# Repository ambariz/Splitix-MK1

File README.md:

# Splitix MK1

A custom, split mechanical keyboard with modular design, it can be used as a split keyboard or joined together and used like a regular keyboard.

Inspired by the split, futuristic keyboard used by Tony Stark in Iron Man, this project explores that concept in a practical, physical form. Splitix MK1 is the first iteration, focused on building a solid foundation before moving towards more advanced designs.

It features a custom PCB designed in KiCad, per-key NeoPixel RGB lighting, an integrated display, and a rotary encoder. The board also includes battery support with voltage monitoring.

The design includes a fully hand-routed PCB with custom footprints and a skeletal 3D-printed case that enhances the lighting and overall aesthetic.

This project is part of a larger journey toward creating a more advanced, Iron Man - inspired keyboard in future iterations.

| Left Build (without case) | Right Build (without case) |
|-----------|------------|
|  |  |

# Features

- Split / Modular (can be joined and used as a single keyboard)
- Wireless (Bluetooth via NRF52840)
- ZMK Firmware
- Hotswappable
- Per-key NeoPixel RGB
- Rotary Encoder
- Integrated Display
- Skeletal 3D-printed case (M3 mount)

## CAD

> **Note:**
> This is a skeletal open case design that includes only the base structure. It is designed to hold the PCB securely while keeping the overall form minimal and exposing the components, especially the RGB lighting. The open design enhances visibility of the internals and lighting, while support pillars and M3 mounts provide the necessary structural stability.

| Left | Right |
|------|-------|
|  |  |
|  |  |
|  |  |

## PCB

> **Note:**  
> The PCB is designed as a single board with mouse bite connections, allowing it to be snapped into left and right halves after fabrication.

## Schematic

> **Note:**  
> The preview images may be scaled down and lose detail. Use the PDF below for a clear, full-resolution view.

<p align="center">
  
</p>

| Left | Right |
|------|-------|
|  |  |

## ZMK Keymap

## BOM

| Product | Quantity | Source | Price (INR) | Link |
| :--- | :--- | :--- | :--- | :--- |
| ProMicro NRF52840 | 2 | Robu | 1516 | [Product Link](https://robu.in/product/promicro-nrf52840-development-board/) <br> OR <br> [Product Link](https://robu.in/product/pro-micro-nrf52840-development-board-compatible-with-nicenano-v2-0/) <br> OR <br> [Product Link](https://probots.co.in/pro-micro-nrf52840-development-board-compatible-with-nice-nano-v2-0.html)|
| Hongyan EC11H 7CE20P1ZD20 | 2 | Robu | 110 | [Product Link](https://robu.in/product/hongyan-ec11h-7ce20p1zd20-rotary-encoder-with-push-button-switch-vertical-plug-in-5-pin/) |
| EC11 Rotary Encoder Knob (D-shaft) | 2 | Robu | 58 | [Product Link](https://robu.in/product/potentiometer-knob-rotary-switch-cap-black-color-pack-of-5-pcs/) |
| 0.96" / 1.3" I2C OLED | 2 | Robu | 312 | [Product Link](https://robu.in/product/0-96-inch-yellow-yellow-blue-oled-lcd-led-display-module/) <br> OR <br> [Product Link](https://robu.in/product/1-3-inch-i2c-iic-4-pin-oled-display-module-with-vcc-gnd-blue/) |
| WS2812B 16-LED Ring (Neopixel) | 6 (rings) / 90 (individual) | Robu / Ktron | 546 | [Product Link](https://robu.in/product/16bit-ws2812b-5050-rgb-led-built-in-full-color-driving-lights-circular-development-board/) <br> OR <br> [Product Link](https://www.ktron.in/product/ws2812b-rgb-smd-5050-led/?v=c86ee0d9d7ed) |
| 330Ω Resistor | 4 | Robu | 1.16 | [Product Link](https://robu.in/product/330-ohm-0-25w-metal-film-resistor-pack-of-100/) |
| 806kΩ Resistor | 2 | Robu | 1.24 | [Product Link](https://robu.in/product/mcmf0w4ff8203a50-multicomp-pro-metal-film-resistor-820kohm-250mw-1/) |
| 2MΩ Resistor | 2 | Amazon | 198 | [Product Link](https://www.amazon.in/Electronic-Spices-Tolerance-Through-Resistors/dp/B0BDDRD9DN) |
| 100µF 0805 Capacitor | 6 | Robu | 270 | [Product Link](https://robu.in/product/cl21a107mqynnwe-samsang-6-3v-100uf-x5r-%C2%B120-0805-multilayer-ceramic-capacitors-mlcc-smd-smt-rohs/) |
| 0.1µF (100nF) 0805 Capacitor | 95 | Robu | 145.35 | [Product Link](https://robu.in/product/cc0805jrx7r9bb104-yageo-smd-multilayer-ceramic-capacitor-0-1-%C2%B5f-50-v-0805-2012-metric-%C2%B1-5-x7r-cc-series/) |
| Mechanical Key Switches (MX Compatible) | 75 | StacksKB | 2398 | [Product Link](https://stackskb.com/store/akko-creamy-cyan-switch-pack-of-45-pre-order/) |
| Keycaps (MX Compatible) | 1 set | StacksKB | 1299 | [Product Link](https://stackskb.com/store/veekos-gradient-keycaps-cherry-profile-135-keys/) |
| Hotswap Sockets (Kailh MX) | 75 | StacksKB | 750 | [Product Link](https://stackskb.com/store/ttc-pokayoke-hotswap-sockets-v2-10000-cycles/) |
| 1N4148 Diodes | 80 | StacksKB | 120 | [Product Link](https://stackskb.com/store/1n4148-through-hole-diode/) |
| Li-ion Battery 1500mAh | 2 | Robu | 502 | [Product Link](https://robu.in/product/nova-803450-1500mah-3-7v-lipo-battery-pack/) |
| JST-PH 2-pin Connector | 2 | Robu | 2.84 | [Product Link](https://robu.in/product/jst-sh-2-pin-connector-2mm-pitch/) |
| TP4056 Type-C Charging Module | 2 | Robu | 28 | [Product Link](https://robu.in/product/tp4056-1a-li-ion-lithium-battery-charging-module-with-current-protection-type-c/) |
| Slide Switch SS-12D03 | 2 | Robu | 6 | [Product Link](https://robu.in/product/slide-switch-ss-12d03-1p2t/) |
| Keyboard PCB Left | 5 | Robu | 2500 | [Product Link](https://robu.in/product/online-pcb-manufacturing-service/) |
| Keyboard PCB Right | 5 | Robu | 2500 | [Product Link](https://robu.in/product/online-pcb-manufacturing-service/) |
| Keyboard Case (3D Print) | 1 | Robu | 530 | [Product Link](https://robu.in/product/3d-printing-service/) |
| Screws | 15 | Generic |  | Any M3 screws will work |

---

### Total Cost (Maximum)

**₹13,793.59**

> Includes all components for full build.

---

# Mechanical Keyboard Keycap Profiles

---

### Quick Comparison
| Profile | Key Features | Best Used For |
| :--- | :--- | :--- |
| **Cherry** | Ergonomic height, reduces accidental touches. | All-around daily use. |
| **OEM** | Standard height, crisp typing sound. | Linear switches and gaming. |
| **XDA** | Uniform height, large surface area. | Tactile switches, long typing sessions. |
| **DSA** | Very low, uniform height. | Minimalist builds and customization. |
| **MDA** | Stepped uniform profile, textured feel. | Ergonomic long-form typing. |
| **SA** | Tallest profile, spherical sculpt. | Aesthetics and deep sound (requires wrist rest). |

---

> ### Note:
- **Tall Profiles (SA):** Better acoustics and aesthetics, but poor ergonomics without a wrist rest.  
- **Flat Profiles (XDA, DSA):** Easier to customize looks, but higher chance of mistyping.  
- **Sculpted Profiles (Cherry, OEM, MDA):** Best for typing speed and overall accuracy.  

---

# Keyswitch Selection Guide

| Type | Characteristics | Best For |
| :--- | :--- | :--- |
| **1️⃣ Linear** | Very smooth, no bump. Quiet unless bottom-out → nice thock | Gaming + smooth typing |
| **2️⃣ Tactile** | Noticeable bump mid-press. Balanced sound + feel | Typing |
| **3️⃣ Clicky** | Loud click + tactile bump. Very audible → polarizing | Enthusiasts who love feedback |
| **4️⃣ Low Profile** | Short travel → less thock. More functional than aesthetic | Portable/compact builds |
| **5️⃣ Silent Switches** | Dampened + muted. Almost no sound → office safe | Office environments |  

marbastlib
keyswitch kicad library
keyboard footprints placer
fabrucatuib toolkit

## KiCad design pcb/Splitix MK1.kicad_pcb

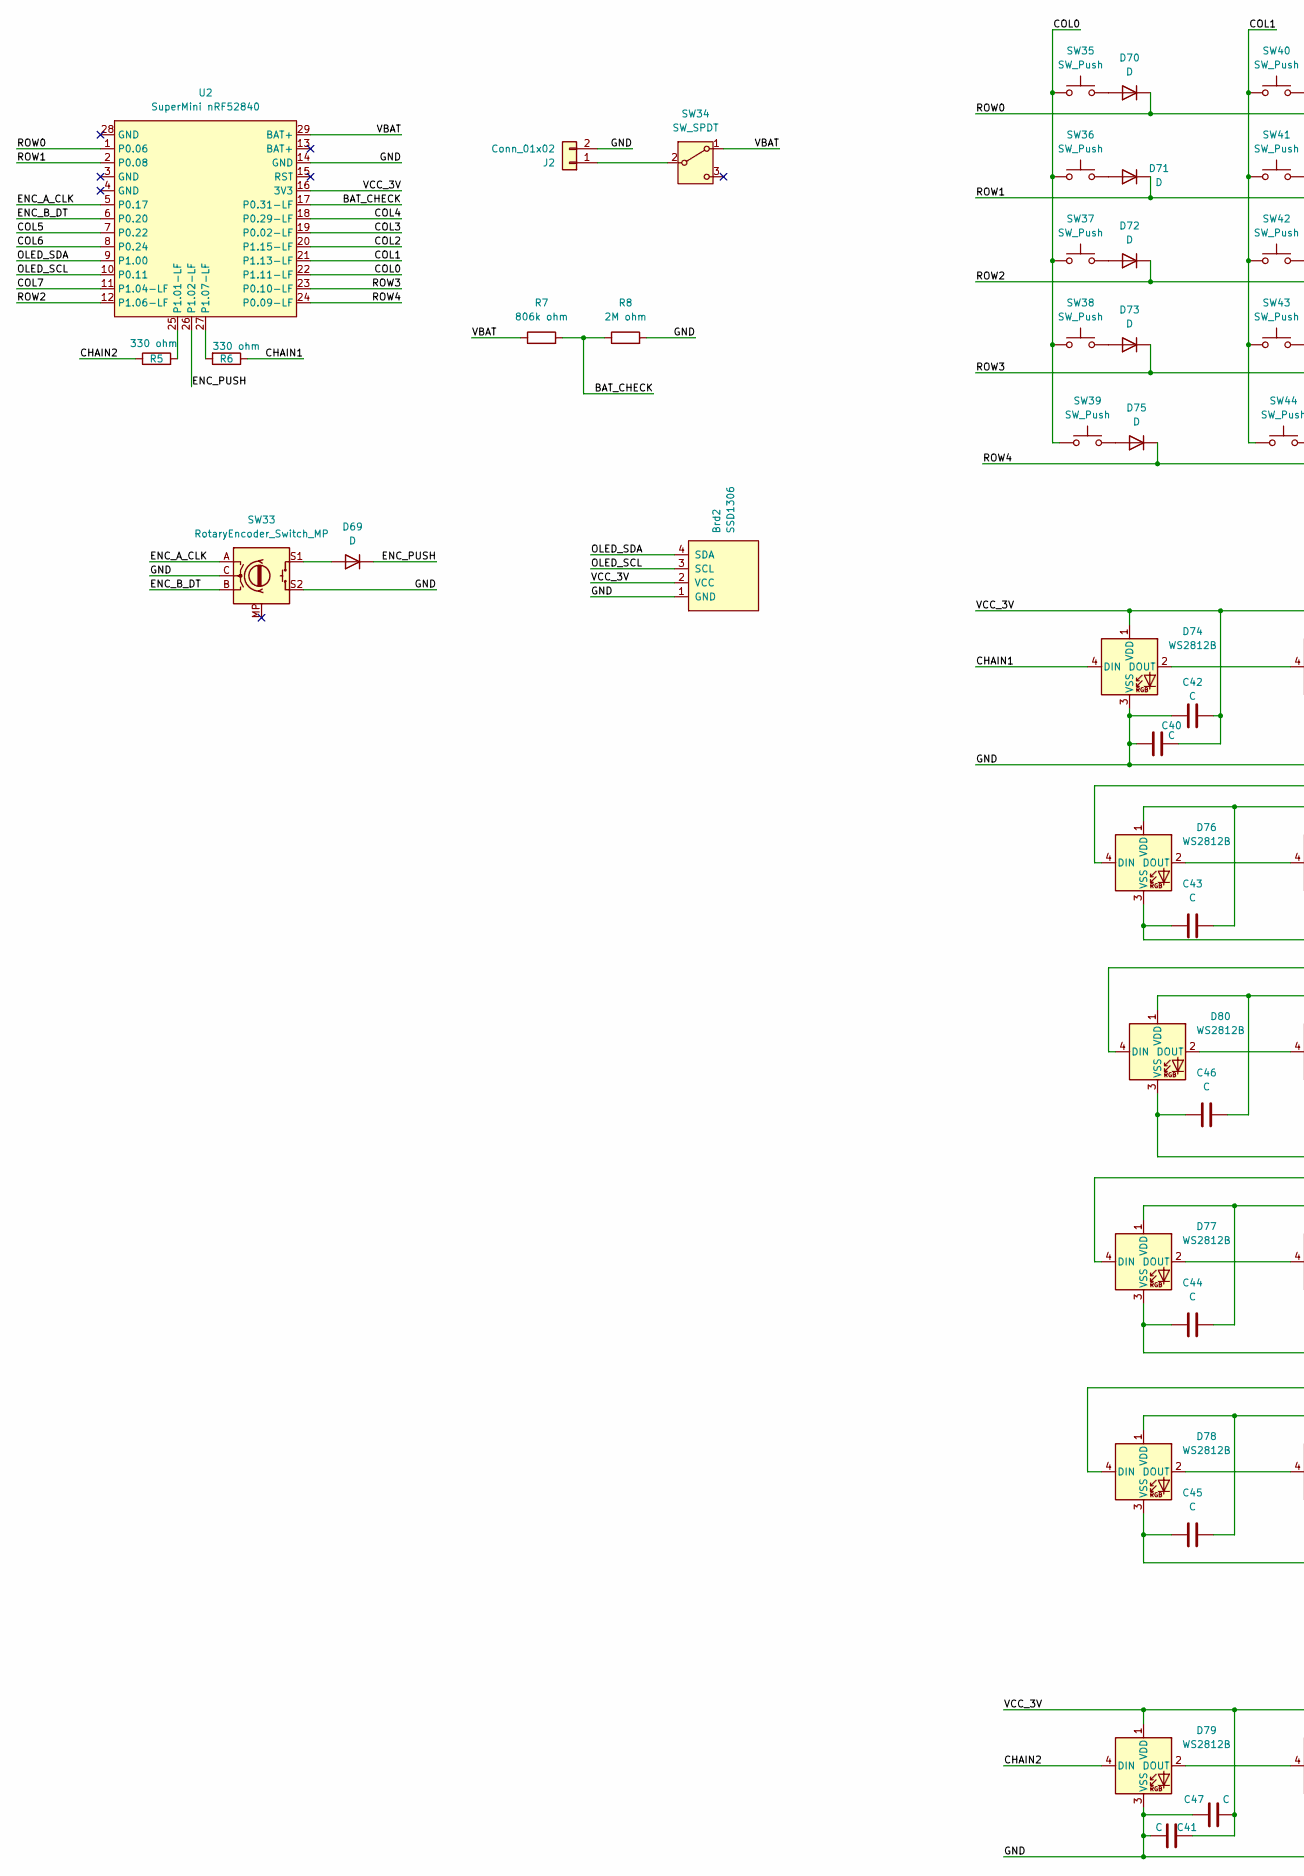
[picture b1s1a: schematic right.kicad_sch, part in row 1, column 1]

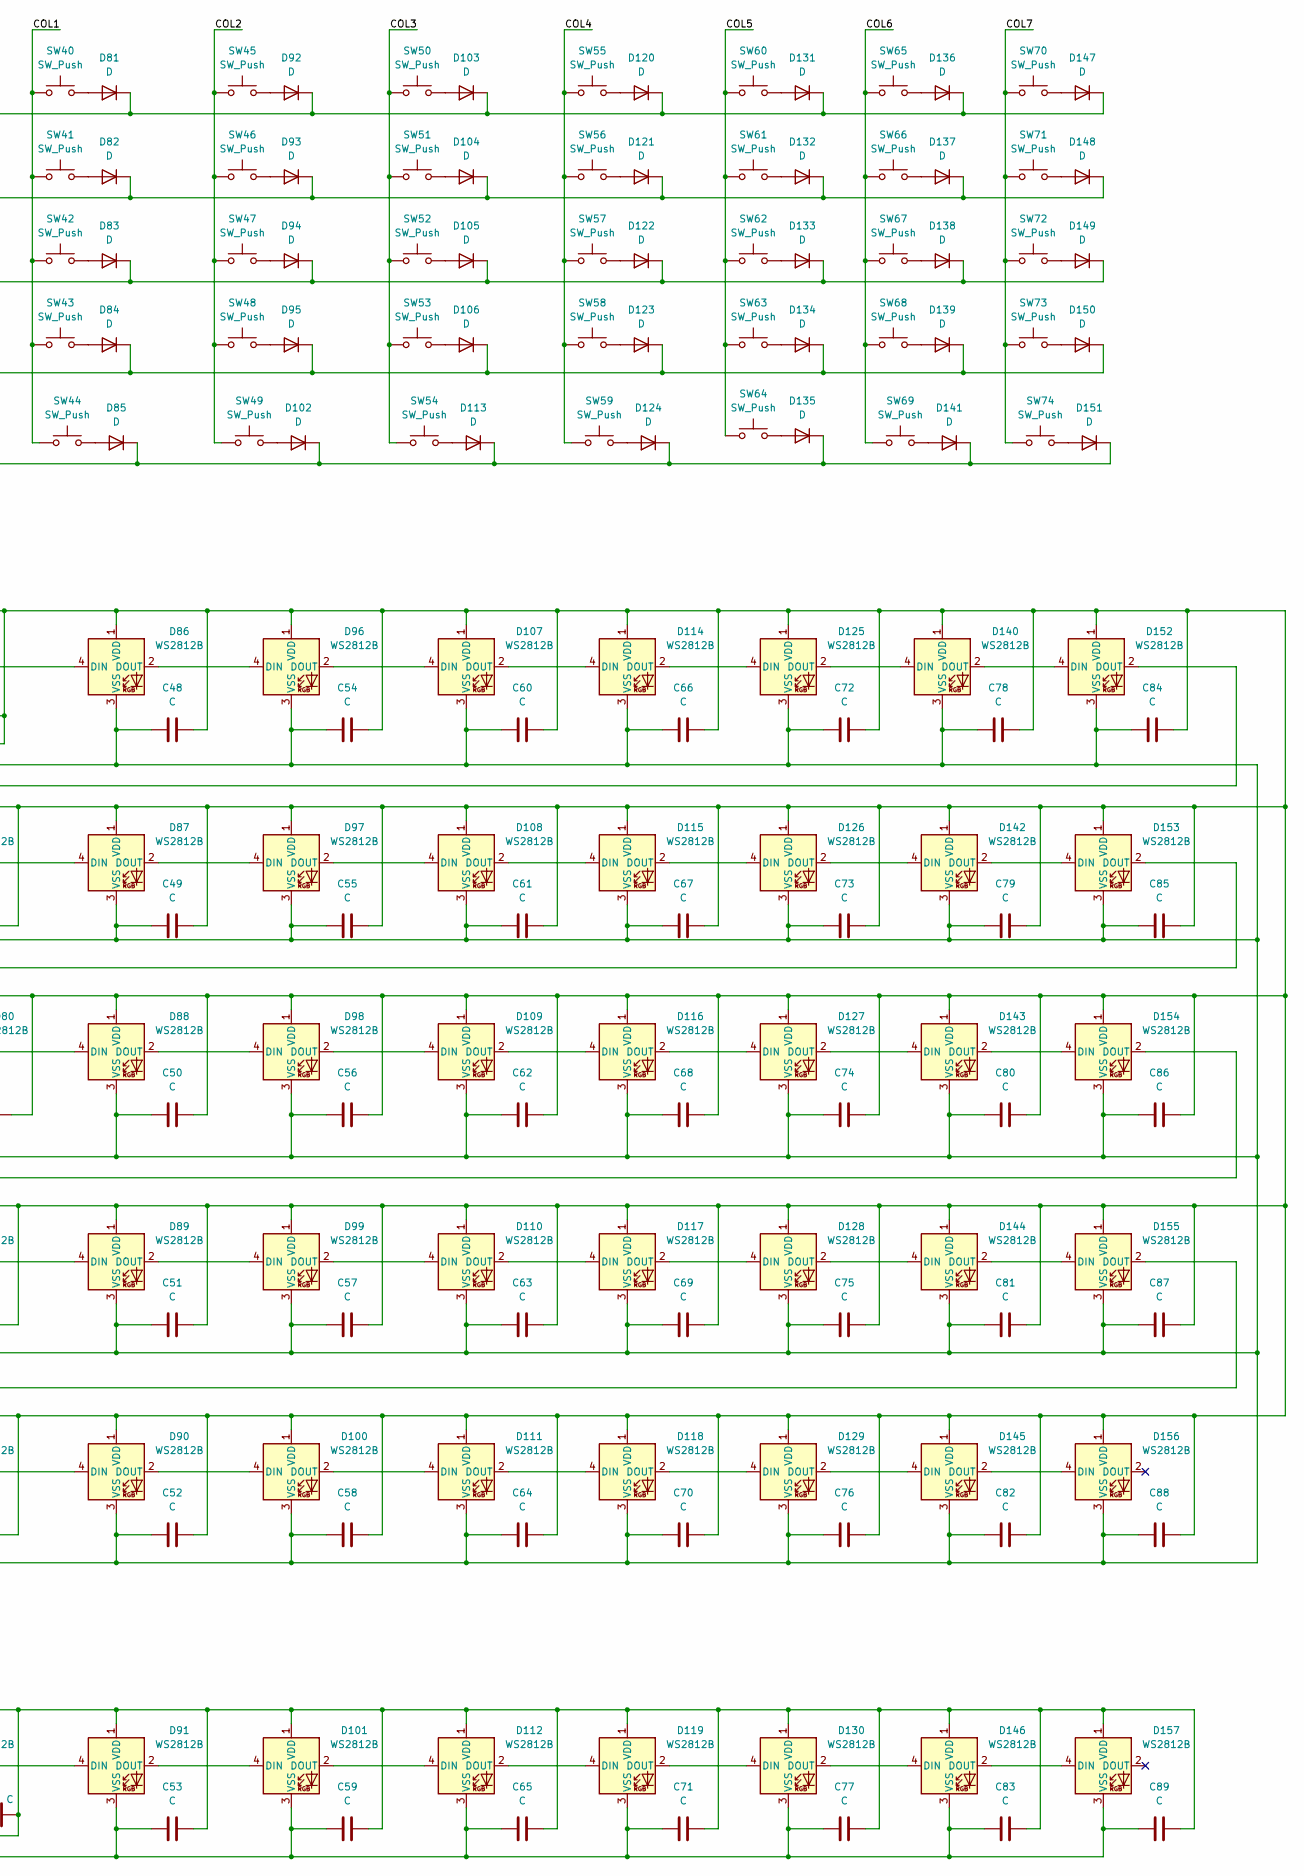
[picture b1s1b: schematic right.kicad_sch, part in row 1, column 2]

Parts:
Brd2: SSD1306; 128x64OLED
C40, C41, C42, C43, C44, C45, C46, C47, C48, C49, C50, C51, C52, C53, C54, C55, C56, C57, C58, C59, C60, C61, C62, C63, C64, C65, C66, C67, C68, C69, C70, C71, C72, C73, C74, C75, C76, C77, C78, C79, C80, C81, C82, C83, C84, C85, C86, C87, C88, C89: C; C_0805_2012Metric_Pad1.18x1.45mm_HandSolder
D69, D70, D71, D72, D73, D75, D81, D82, D83, D84, D85, D92, D93, D94, D95, D102, D103, D104, D105, D106, D113, D120, D121, D122, D123, D124, D131, D132, D133, D134, D135, D136, D137, D138, D139, D141, D147, D148, D149, D150, D151: D; D_DO-35_SOD27_P7.62mm_Horizontal
D74, D76, D77, D78, D80, D86, D87, D88, D89, D90, D96, D97, D98, D99, D100, D107, D108, D109, D110, D111, D114, D115, D116, D117, D118, D125, D126, D127, D128, D129, D140, D142, D143, D144, D145, D152, D153, D154, D155, D156: WS2812B; WS2812B_5050_reversed_SMD_edge
D79, D91, D101, D112, D119, D130, D146, D157: WS2812B; WS2812B_5050_reversed_SMD_strip
J2: Conn_01x02; PinHeader_1x02_P2.54mm_Vertical
R5, R6: 330 ohm; R_Axial_DIN0207_L6.3mm_D2.5mm_P7.62mm_Horizontal
R7: 806k ohm; R_Axial_DIN0207_L6.3mm_D2.5mm_P7.62mm_Horizontal
R8: 2M ohm; R_Axial_DIN0207_L6.3mm_D2.5mm_P7.62mm_Horizontal
SW33: RotaryEncoder_Switch_MP; RotaryEncoder_Alps_EC11E-Switch_Vertical_H20mm_CircularMoun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
SW34: SW_SPDT; PinHeader_1x03_P2.54mm_Vertical
SW35, SW36, SW37, SW38, SW40, SW41, SW42, SW43, SW45, SW46, SW47, SW48, SW49, SW50, SW51, SW52, SW53, SW54, SW55, SW56, SW57, SW58, SW59, SW60, SW61, SW62, SW64, SW66, SW68, SW69, SW70, SW72, SW73, SW74: SW_Push; SW_MX_HS_KS-2P02B01-01_1u
SW39: SW_Push; SW_MX_HS_KS-2P02B01-01_2.75u
SW44: SW_Push; SW_MX_HS_KS-2P02B01-01_1.25u
SW63: SW_Push; SW_MX_HS_KS-2P02B01-01_1.75u
SW65: SW_Push; SW_MX_HS_KS-2P02B01-01_2u
SW67: SW_Push; SW_MX_HS_KS-2P02B01-01_2.25u
SW71: SW_Push; SW_MX_HS_KS-2P02B01-01_1.5u
U2: SuperMini nRF52840; SuperMini_nRF52840_AH_USBup

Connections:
/right/BAT_CHECK: R7.2, R8.1, U2.17 (P0.31-LF)
/right/CHAIN1: D74.4 (DIN), R6.1
/right/CHAIN2: D79.4 (DIN), R5.1
/right/COL0: SW35.1, SW36.1, SW37.1, SW38.1, SW39.1, U2.22 (P1.11-LF)
/right/COL1: SW40.1, SW41.1, SW42.1, SW43.1, SW44.1, U2.21 (P1.13-LF)
/right/COL2: SW45.1, SW46.1, SW47.1, SW48.1, SW49.1, U2.20 (P1.15-LF)
/right/COL3: SW50.1, SW51.1, SW52.1, SW53.1, SW54.1, U2.19 (P0.02-LF)
/right/COL4: SW55.1, SW56.1, SW57.1, SW58.1, SW59.1, U2.18 (P0.29-LF)
/right/COL5: SW60.1, SW61.1, SW62.1, SW63.1, SW64.1, U2.7 (P0.22)
/right/COL6: SW65.1, SW66.1, SW67.1, SW68.1, SW69.1, U2.8 (P0.24)
/right/COL7: SW70.1, SW71.1, SW72.1, SW73.1, SW74.1, U2.11 (P1.04-LF)
/right/ENC_A_CLK: SW33.A, U2.5 (P0.17)
/right/ENC_B_DT: SW33.B, U2.6 (P0.20)
/right/ENC_PUSH: D69.1 (K), U2.26 (P1.02-LF)
/right/GND: Brd2.1 (GND), C40.1, C41.1, C42.1, C43.1, C44.1, C45.1, C46.1, C47.1, C48.1, C49.1, C50.1, C51.1, C52.1, C53.1, C54.1, C55.1, C56.1, C57.1, C58.1, C59.1, C60.1, C61.1, C62.1, C63.1, C64.1, C65.1, C66.1, C67.1, C68.1, C69.1, C70.1, C71.1, C72.1, C73.1, C74.1, C75.1, C76.1, C77.1, C78.1, C79.1, C80.1, C81.1, C82.1, C83.1, C84.1, C85.1, C86.1, C87.1, C88.1, C89.1, D74.3 (VSS), D76.3 (VSS), D77.3 (VSS), D78.3 (VSS), D79.3 (VSS), D80.3 (VSS), D86.3 (VSS), D87.3 (VSS), D88.3 (VSS), D89.3 (VSS), D90.3 (VSS), D91.3 (VSS), D96.3 (VSS), D97.3 (VSS), D98.3 (VSS), D99.3 (VSS), D100.3 (VSS), D101.3 (VSS), D107.3 (VSS), D108.3 (VSS), D109.3 (VSS), D110.3 (VSS), D111.3 (VSS), D112.3 (VSS), D114.3 (VSS), D115.3 (VSS), D116.3 (VSS), D117.3 (VSS), D118.3 (VSS), D119.3 (VSS), D125.3 (VSS), D126.3 (VSS), D127.3 (VSS), D128.3 (VSS), D129.3 (VSS), D130.3 (VSS), D140.3 (VSS), D142.3 (VSS), D143.3 (VSS), D144.3 (VSS), D145.3 (VSS), D146.3 (VSS), D152.3 (VSS), D153.3 (VSS), D154.3 (VSS), D155.3 (VSS), D156.3 (VSS), D157.3 (VSS), J2.2, R8.2, SW33.C, SW33.S2, U2.14 (GND)
/right/OLED_SCL: Brd2.3 (SCL), U2.10 (P0.11)
/right/OLED_SDA: Brd2.4 (SDA), U2.9 (P1.00)
/right/ROW0: D70.1 (K), D81.1 (K), D92.1 (K), D103.1 (K), D120.1 (K), D131.1 (K), D136.1 (K), D147.1 (K), U2.1 (P0.06)
/right/ROW1: D71.1 (K), D82.1 (K), D93.1 (K), D104.1 (K), D121.1 (K), D132.1 (K), D137.1 (K), D148.1 (K), U2.2 (P0.08)
/right/ROW2: D72.1 (K), D83.1 (K), D94.1 (K), D105.1 (K), D122.1 (K), D133.1 (K), D138.1 (K), D149.1 (K), U2.12 (P1.06-LF)
/right/ROW3: D73.1 (K), D84.1 (K), D95.1 (K), D106.1 (K), D123.1 (K), D134.1 (K), D139.1 (K), D150.1 (K), U2.23 (P0.10-LF)
/right/ROW4: D75.1 (K), D85.1 (K), D102.1 (K), D113.1 (K), D124.1 (K), D135.1 (K), D141.1 (K), D151.1 (K), U2.24 (P0.09-LF)
/right/VBAT: R7.1, SW34.1 (A), U2.29 (BAT+)
/right/VCC_3V: Brd2.2 (VCC), C40.2, C41.2, C42.2, C43.2, C44.2, C45.2, C46.2, C47.2, C48.2, C49.2, C50.2, C51.2, C52.2, C53.2, C54.2, C55.2, C56.2, C57.2, C58.2, C59.2, C60.2, C61.2, C62.2, C63.2, C64.2, C65.2, C66.2, C67.2, C68.2, C69.2, C70.2, C71.2, C72.2, C73.2, C74.2, C75.2, C76.2, C77.2, C78.2, C79.2, C80.2, C81.2, C82.2, C83.2, C84.2, C85.2, C86.2, C87.2, C88.2, C89.2, D74.1 (VDD), D76.1 (VDD), D77.1 (VDD), D78.1 (VDD), D79.1 (VDD), D80.1 (VDD), D86.1 (VDD), D87.1 (VDD), D88.1 (VDD), D89.1 (VDD), D90.1 (VDD), D91.1 (VDD), D96.1 (VDD), D97.1 (VDD), D98.1 (VDD), D99.1 (VDD), D100.1 (VDD), D101.1 (VDD), D107.1 (VDD), D108.1 (VDD), D109.1 (VDD), D110.1 (VDD), D111.1 (VDD), D112.1 (VDD), D114.1 (VDD), D115.1 (VDD), D116.1 (VDD), D117.1 (VDD), D118.1 (VDD), D119.1 (VDD), D125.1 (VDD), D126.1 (VDD), D127.1 (VDD), D128.1 (VDD), D129.1 (VDD), D130.1 (VDD), D140.1 (VDD), D142.1 (VDD), D143.1 (VDD), D144.1 (VDD), D145.1 (VDD), D146.1 (VDD), D152.1 (VDD), D153.1 (VDD), D154.1 (VDD), D155.1 (VDD), D156.1 (VDD), D157.1 (VDD), U2.16 (3V3)
unnamed: D69.2 (A), SW33.S1
unnamed: D70.2 (A), SW35.2
unnamed: D71.2 (A), SW36.2
unnamed: D72.2 (A), SW37.2
unnamed: D73.2 (A), SW38.2
unnamed: D74.2 (DOUT), D86.4 (DIN)
unnamed: D75.2 (A), SW39.2
unnamed: D76.2 (DOUT), D87.4 (DIN)
unnamed: D77.2 (DOUT), D89.4 (DIN)
unnamed: D78.2 (DOUT), D90.4 (DIN)
unnamed: D79.2 (DOUT), D91.4 (DIN)
unnamed: D80.2 (DOUT), D88.4 (DIN)
unnamed: D81.2 (A), SW40.2
unnamed: D82.2 (A), SW41.2
unnamed: D83.2 (A), SW42.2
unnamed: D84.2 (A), SW43.2
unnamed: D85.2 (A), SW44.2
unnamed: D86.2 (DOUT), D96.4 (DIN)
unnamed: D87.2 (DOUT), D97.4 (DIN)
unnamed: D88.2 (DOUT), D98.4 (DIN)
unnamed: D89.2 (DOUT), D99.4 (DIN)
unnamed: D92.2 (A), SW45.2
unnamed: D93.2 (A), SW46.2
unnamed: D94.2 (A), SW47.2
unnamed: D95.2 (A), SW48.2
unnamed: D90.2 (DOUT), D100.4 (DIN)
unnamed: D100.2 (DOUT), D111.4 (DIN)
unnamed: D91.2 (DOUT), D101.4 (DIN)
unnamed: D101.2 (DOUT), D112.4 (DIN)
unnamed: D102.2 (A), SW49.2
unnamed: D103.2 (A), SW50.2
unnamed: D104.2 (A), SW51.2
unnamed: D105.2 (A), SW52.2
unnamed: D106.2 (A), SW53.2
unnamed: D96.2 (DOUT), D107.4 (DIN)
unnamed: D107.2 (DOUT), D114.4 (DIN)
unnamed: D97.2 (DOUT), D108.4 (DIN)
unnamed: D108.2 (DOUT), D115.4 (DIN)
unnamed: D98.2 (DOUT), D109.4 (DIN)
unnamed: D109.2 (DOUT), D116.4 (DIN)
unnamed: D99.2 (DOUT), D110.4 (DIN)
unnamed: D110.2 (DOUT), D117.4 (DIN)
unnamed: D111.2 (DOUT), D118.4 (DIN)
unnamed: D112.2 (DOUT), D119.4 (DIN)
unnamed: D113.2 (A), SW54.2
unnamed: D114.2 (DOUT), D125.4 (DIN)
unnamed: D115.2 (DOUT), D126.4 (DIN)
unnamed: D116.2 (DOUT), D127.4 (DIN)
unnamed: D117.2 (DOUT), D128.4 (DIN)
unnamed: D118.2 (DOUT), D129.4 (DIN)
unnamed: D119.2 (DOUT), D130.4 (DIN)
unnamed: D120.2 (A), SW55.2
unnamed: D121.2 (A), SW56.2
unnamed: D122.2 (A), SW57.2
unnamed: D123.2 (A), SW58.2
unnamed: D124.2 (A), SW59.2
unnamed: D125.2 (DOUT), D140.4 (DIN)
unnamed: D126.2 (DOUT), D142.4 (DIN)
unnamed: D127.2 (DOUT), D143.4 (DIN)
unnamed: D128.2 (DOUT), D144.4 (DIN)
unnamed: D129.2 (DOUT), D145.4 (DIN)
unnamed: D130.2 (DOUT), D146.4 (DIN)
unnamed: D131.2 (A), SW60.2
unnamed: D132.2 (A), SW61.2
unnamed: D133.2 (A), SW62.2
unnamed: D134.2 (A), SW63.2
unnamed: D135.2 (A), SW64.2
unnamed: D136.2 (A), SW65.2
unnamed: D137.2 (A), SW66.2
unnamed: D138.2 (A), SW67.2
unnamed: D139.2 (A), SW68.2
unnamed: D140.2 (DOUT), D152.4 (DIN)
unnamed: D141.2 (A), SW69.2
unnamed: D142.2 (DOUT), D153.4 (DIN)
unnamed: D143.2 (DOUT), D154.4 (DIN)
unnamed: D144.2 (DOUT), D155.4 (DIN)
unnamed: D145.2 (DOUT), D156.4 (DIN)
unnamed: D146.2 (DOUT), D157.4 (DIN)
unnamed: D147.2 (A), SW70.2
unnamed: D148.2 (A), SW71.2
unnamed: D149.2 (A), SW72.2
unnamed: D150.2 (A), SW73.2
unnamed: D151.2 (A), SW74.2
unnamed: D76.4 (DIN), D152.2 (DOUT)
unnamed: D80.4 (DIN), D153.2 (DOUT)
unnamed: D77.4 (DIN), D154.2 (DOUT)
unnamed: D78.4 (DIN), D155.2 (DOUT)
unnamed: J2.1, SW34.2 (B)
unnamed: R5.2, U2.25 (P1.01-LF)
unnamed: R6.2, U2.27 (P1.07-LF)

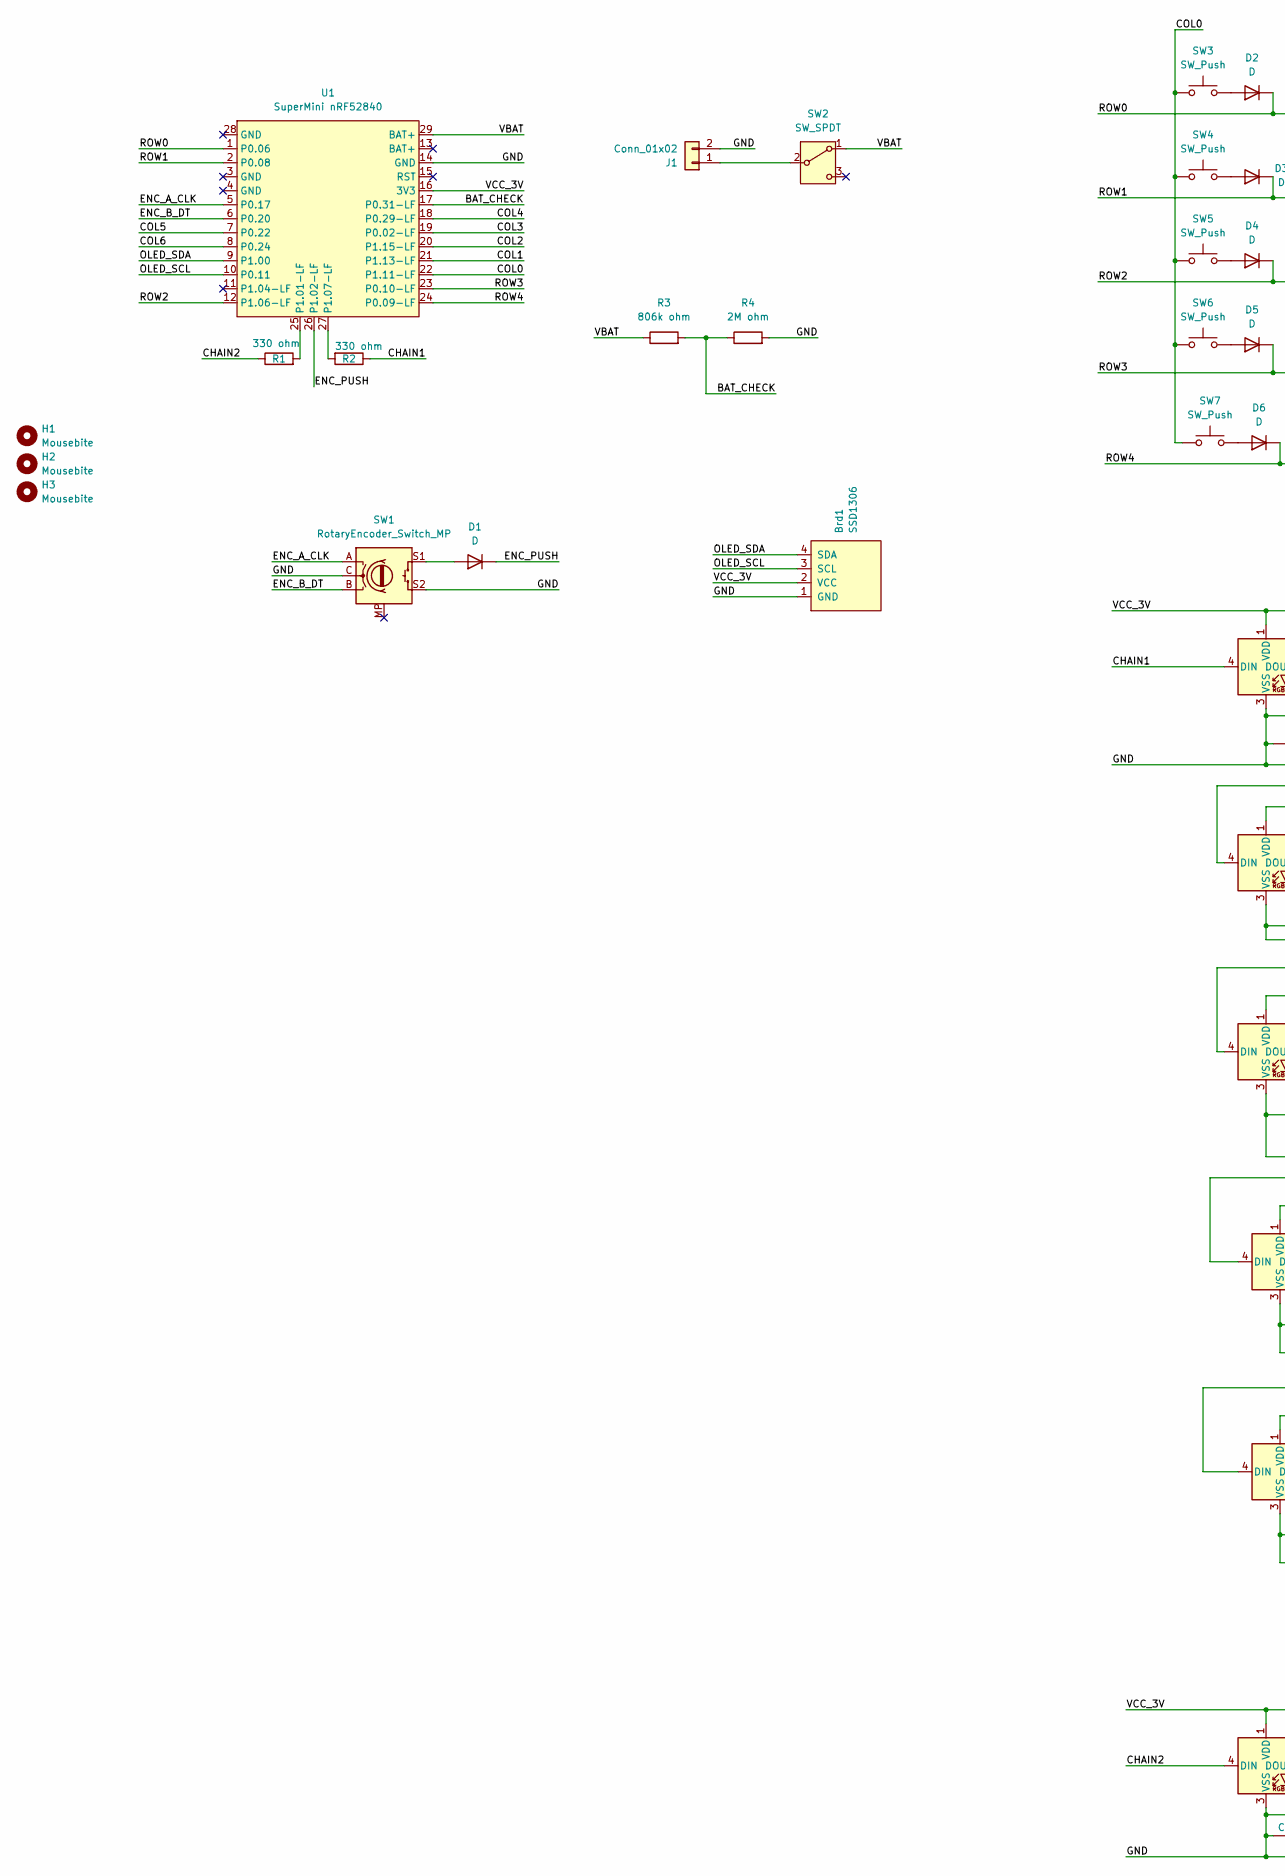
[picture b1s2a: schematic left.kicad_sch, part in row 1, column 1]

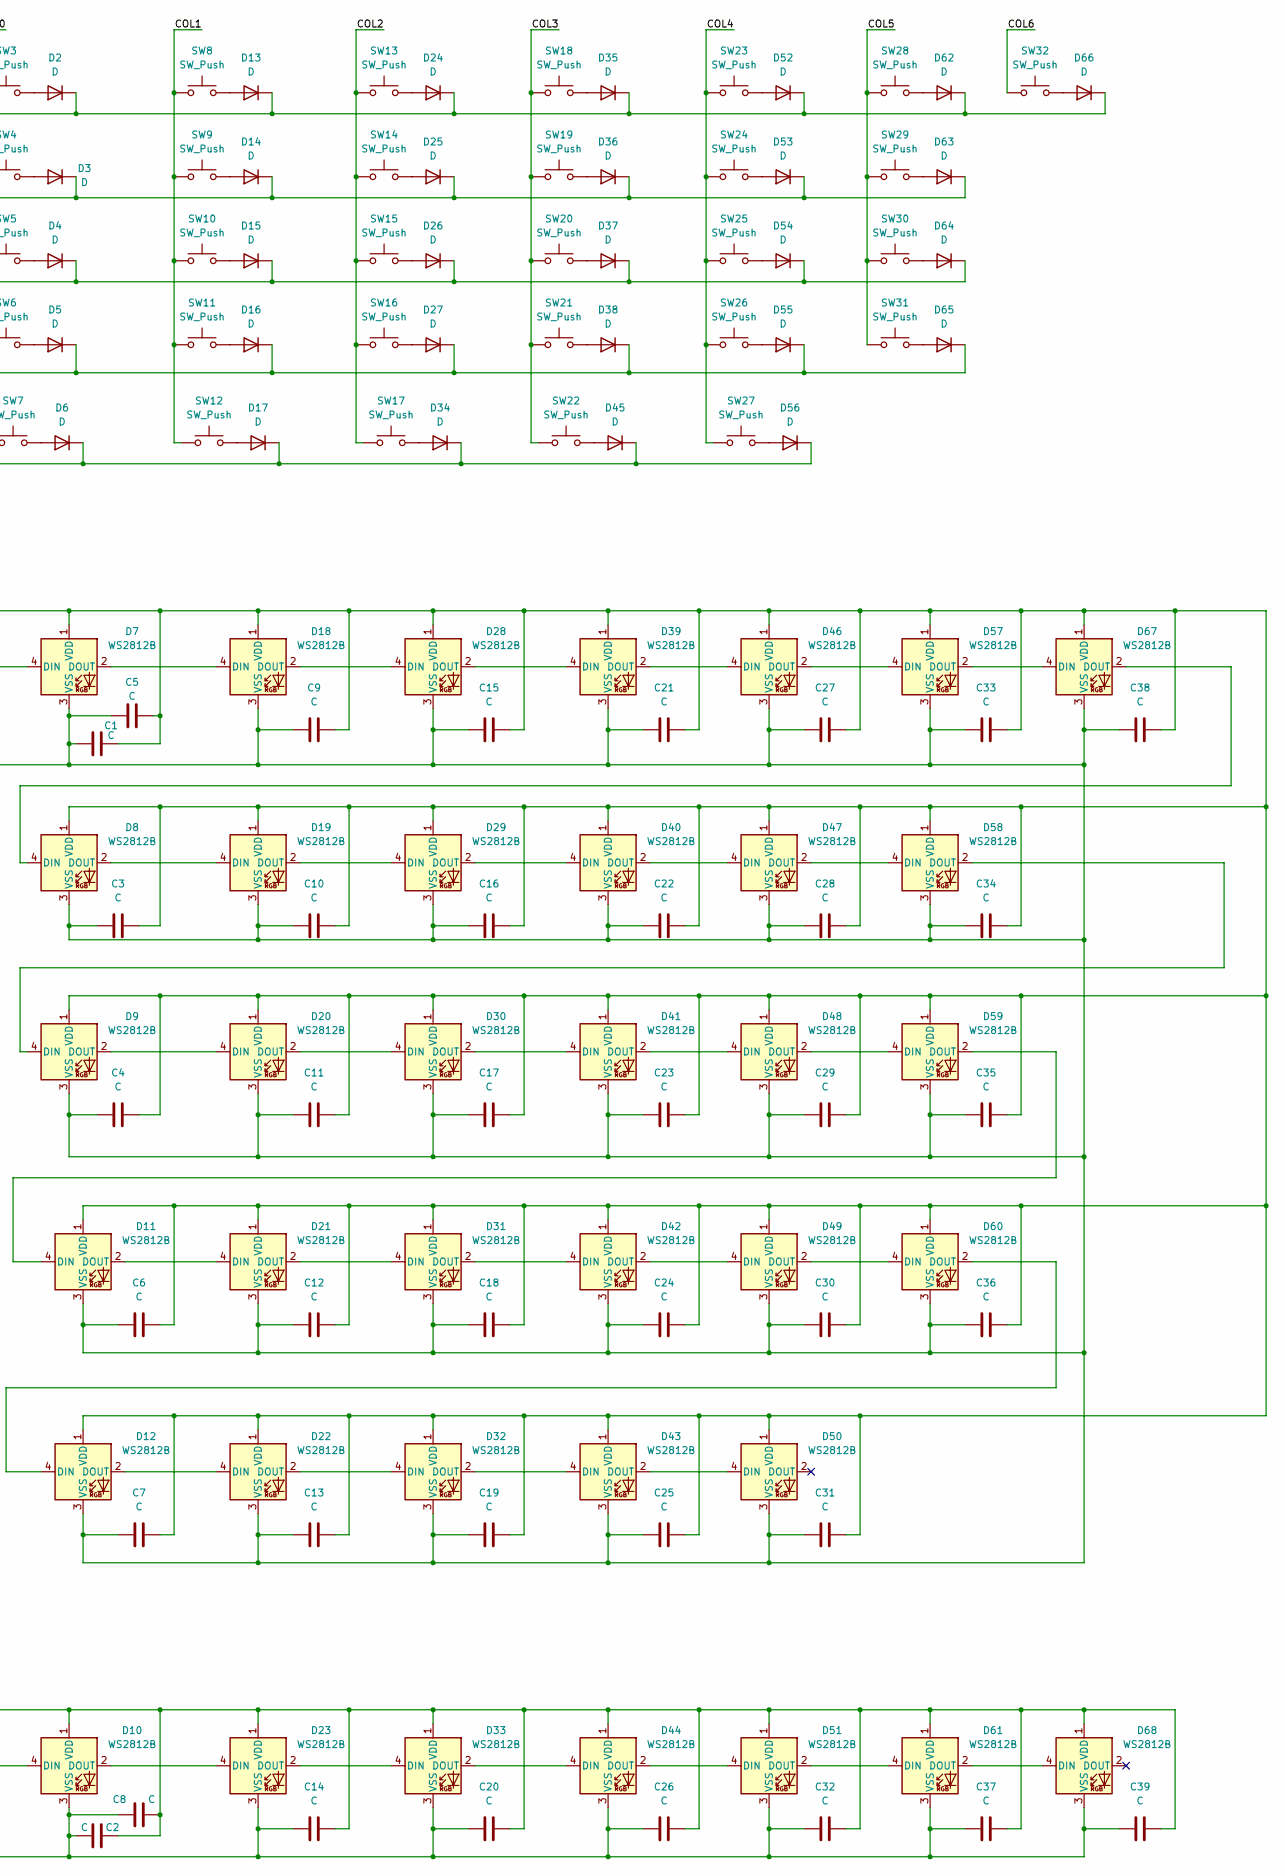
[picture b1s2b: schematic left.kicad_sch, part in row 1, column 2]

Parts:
Brd1: SSD1306; 128x64OLED
C1, C2, C3, C4, C5, C6, C7, C8, C9, C10, C11, C12, C13, C14, C15, C16, C17, C18, C19, C20, C21, C22, C23, C24, C25, C26, C27, C28, C29, C30, C31, C32, C33, C34, C35, C36, C37, C38, C39: C; C_0805_2012Metric_Pad1.18x1.45mm_HandSolder
D1, D2, D3, D4, D5, D6, D13, D14, D15, D16, D17, D24, D25, D26, D27, D34, D35, D36, D37, D38, D45, D52, D53, D54, D55, D56, D62, D63, D64, D65, D66: D; D_DO-35_SOD27_P7.62mm_Horizontal
D7, D8, D9, D11, D12, D18, D19, D20, D21, D22, D28, D29, D30, D31, D32, D39, D40, D41, D42, D43, D46, D47, D48, D49, D50, D57, D58, D59, D60, D67: WS2812B; WS2812B_5050_reversed_SMD_edge
D10, D23, D33, D44, D51, D61, D68: WS2812B; WS2812B_5050_reversed_SMD_strip
H1, H2, H3: Mousebite; MouseBite-Slot_2.0x4.5mm_outset_D0.5mm_P0.85mm_7h
J1: Conn_01x02; PinHeader_1x02_P2.54mm_Vertical
R1, R2: 330 ohm; R_Axial_DIN0207_L6.3mm_D2.5mm_P7.62mm_Horizontal
R3: 806k ohm; R_Axial_DIN0207_L6.3mm_D2.5mm_P7.62mm_Horizontal
R4: 2M ohm; R_Axial_DIN0207_L6.3mm_D2.5mm_P7.62mm_Horizontal
SW1: RotaryEncoder_Switch_MP; RotaryEncoder_Alps_EC11E-Switch_Vertical_H20mm_CircularMoun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
SW2: SW_SPDT; PinHeader_1x03_P2.54mm_Vertical
SW3, SW8, SW9, SW10, SW11, SW13, SW14, SW15, SW16, SW18, SW19, SW20, SW21, SW23, SW24, SW25, SW26, SW28, SW29, SW30, SW31, SW32: SW_Push; SW_MX_HS_KS-2P02B01-01_1u
SW4: SW_Push; SW_MX_HS_KS-2P02B01-01_1.5u
SW5: SW_Push; SW_MX_HS_KS-2P02B01-01_1.75u
SW6: SW_Push; SW_MX_HS_KS-2P02B01-01_2.25u
SW7, SW12, SW17, SW22: SW_Push; SW_MX_HS_KS-2P02B01-01_1.25u
SW27: SW_Push; SW_MX_HS_KS-2P02B01-01_2u
U1: SuperMini nRF52840; SuperMini_nRF52840_AH_USBup

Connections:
/left/BAT_CHECK: R3.2, R4.1, U1.17 (P0.31-LF)
/left/CHAIN1: D7.4 (DIN), R2.1
/left/CHAIN2: D10.4 (DIN), R1.1
/left/COL0: SW3.1, SW4.1, SW5.1, SW6.1, SW7.1, U1.22 (P1.11-LF)
/left/COL1: SW8.1, SW9.1, SW10.1, SW11.1, SW12.1, U1.21 (P1.13-LF)
/left/COL2: SW13.1, SW14.1, SW15.1, SW16.1, SW17.1, U1.20 (P1.15-LF)
/left/COL3: SW18.1, SW19.1, SW20.1, SW21.1, SW22.1, U1.19 (P0.02-LF)
/left/COL4: SW23.1, SW24.1, SW25.1, SW26.1, SW27.1, U1.18 (P0.29-LF)
/left/COL5: SW28.1, SW29.1, SW30.1, SW31.1, U1.7 (P0.22)
/left/COL6: SW32.1, U1.8 (P0.24)
/left/ENC_A_CLK: SW1.A, U1.5 (P0.17)
/left/ENC_B_DT: SW1.B, U1.6 (P0.20)
/left/ENC_PUSH: D1.1 (K), U1.26 (P1.02-LF)
/left/GND: Brd1.1 (GND), C1.1, C2.1, C3.1, C4.1, C5.1, C6.1, C7.1, C8.1, C9.1, C10.1, C11.1, C12.1, C13.1, C14.1, C15.1, C16.1, C17.1, C18.1, C19.1, C20.1, C21.1, C22.1, C23.1, C24.1, C25.1, C26.1, C27.1, C28.1, C29.1, C30.1, C31.1, C32.1, C33.1, C34.1, C35.1, C36.1, C37.1, C38.1, C39.1, D7.3 (VSS), D8.3 (VSS), D9.3 (VSS), D10.3 (VSS), D11.3 (VSS), D12.3 (VSS), D18.3 (VSS), D19.3 (VSS), D20.3 (VSS), D21.3 (VSS), D22.3 (VSS), D23.3 (VSS), D28.3 (VSS), D29.3 (VSS), D30.3 (VSS), D31.3 (VSS), D32.3 (VSS), D33.3 (VSS), D39.3 (VSS), D40.3 (VSS), D41.3 (VSS), D42.3 (VSS), D43.3 (VSS), D44.3 (VSS), D46.3 (VSS), D47.3 (VSS), D48.3 (VSS), D49.3 (VSS), D50.3 (VSS), D51.3 (VSS), D57.3 (VSS), D58.3 (VSS), D59.3 (VSS), D60.3 (VSS), D61.3 (VSS), D67.3 (VSS), D68.3 (VSS), J1.2, R4.2, SW1.C, SW1.S2, U1.14 (GND)
/left/OLED_SCL: Brd1.3 (SCL), U1.10 (P0.11)
/left/OLED_SDA: Brd1.4 (SDA), U1.9 (P1.00)
/left/ROW0: D2.1 (K), D13.1 (K), D24.1 (K), D35.1 (K), D52.1 (K), D62.1 (K), D66.1 (K), U1.1 (P0.06)
/left/ROW1: D3.1 (K), D14.1 (K), D25.1 (K), D36.1 (K), D53.1 (K), D63.1 (K), U1.2 (P0.08)
/left/ROW2: D4.1 (K), D15.1 (K), D26.1 (K), D37.1 (K), D54.1 (K), D64.1 (K), U1.12 (P1.06-LF)
/left/ROW3: D5.1 (K), D16.1 (K), D27.1 (K), D38.1 (K), D55.1 (K), D65.1 (K), U1.23 (P0.10-LF)
/left/ROW4: D6.1 (K), D17.1 (K), D34.1 (K), D45.1 (K), D56.1 (K), U1.24 (P0.09-LF)
/left/VBAT: R3.1, SW2.1 (A), U1.29 (BAT+)
/left/VCC_3V: Brd1.2 (VCC), C1.2, C2.2, C3.2, C4.2, C5.2, C6.2, C7.2, C8.2, C9.2, C10.2, C11.2, C12.2, C13.2, C14.2, C15.2, C16.2, C17.2, C18.2, C19.2, C20.2, C21.2, C22.2, C23.2, C24.2, C25.2, C26.2, C27.2, C28.2, C29.2, C30.2, C31.2, C32.2, C33.2, C34.2, C35.2, C36.2, C37.2, C38.2, C39.2, D7.1 (VDD), D8.1 (VDD), D9.1 (VDD), D10.1 (VDD), D11.1 (VDD), D12.1 (VDD), D18.1 (VDD), D19.1 (VDD), D20.1 (VDD), D21.1 (VDD), D22.1 (VDD), D23.1 (VDD), D28.1 (VDD), D29.1 (VDD), D30.1 (VDD), D31.1 (VDD), D32.1 (VDD), D33.1 (VDD), D39.1 (VDD), D40.1 (VDD), D41.1 (VDD), D42.1 (VDD), D43.1 (VDD), D44.1 (VDD), D46.1 (VDD), D47.1 (VDD), D48.1 (VDD), D49.1 (VDD), D50.1 (VDD), D51.1 (VDD), D57.1 (VDD), D58.1 (VDD), D59.1 (VDD), D60.1 (VDD), D61.1 (VDD), D67.1 (VDD), D68.1 (VDD), U1.16 (3V3)
unnamed: D1.2 (A), SW1.S1
unnamed: D2.2 (A), SW3.2
unnamed: D3.2 (A), SW4.2
unnamed: D4.2 (A), SW5.2
unnamed: D5.2 (A), SW6.2
unnamed: D6.2 (A), SW7.2
unnamed: D10.2 (DOUT), D23.4 (DIN)
unnamed: D11.4 (DIN), D59.2 (DOUT)
unnamed: D11.2 (DOUT), D21.4 (DIN)
unnamed: D12.4 (DIN), D60.2 (DOUT)
unnamed: D12.2 (DOUT), D22.4 (DIN)
unnamed: D13.2 (A), SW8.2
unnamed: D14.2 (A), SW9.2
unnamed: D15.2 (A), SW10.2
unnamed: D16.2 (A), SW11.2
unnamed: D17.2 (A), SW12.2
unnamed: D7.2 (DOUT), D18.4 (DIN)
unnamed: D18.2 (DOUT), D28.4 (DIN)
unnamed: D8.2 (DOUT), D19.4 (DIN)
unnamed: D19.2 (DOUT), D29.4 (DIN)
unnamed: D9.2 (DOUT), D20.4 (DIN)
unnamed: D20.2 (DOUT), D30.4 (DIN)
unnamed: D21.2 (DOUT), D31.4 (DIN)
unnamed: D22.2 (DOUT), D32.4 (DIN)
unnamed: D23.2 (DOUT), D33.4 (DIN)
unnamed: D24.2 (A), SW13.2
unnamed: D25.2 (A), SW14.2
unnamed: D26.2 (A), SW15.2
unnamed: D27.2 (A), SW16.2
unnamed: D28.2 (DOUT), D39.4 (DIN)
unnamed: D29.2 (DOUT), D40.4 (DIN)
unnamed: D30.2 (DOUT), D41.4 (DIN)
unnamed: D31.2 (DOUT), D42.4 (DIN)
unnamed: D32.2 (DOUT), D43.4 (DIN)
unnamed: D33.2 (DOUT), D44.4 (DIN)
unnamed: D34.2 (A), SW17.2
unnamed: D35.2 (A), SW18.2
unnamed: D36.2 (A), SW19.2
unnamed: D37.2 (A), SW20.2
unnamed: D38.2 (A), SW21.2
unnamed: D39.2 (DOUT), D46.4 (DIN)
unnamed: D40.2 (DOUT), D47.4 (DIN)
unnamed: D41.2 (DOUT), D48.4 (DIN)
unnamed: D42.2 (DOUT), D49.4 (DIN)
unnamed: D43.2 (DOUT), D50.4 (DIN)
unnamed: D44.2 (DOUT), D51.4 (DIN)
unnamed: D45.2 (A), SW22.2
unnamed: D46.2 (DOUT), D57.4 (DIN)
unnamed: D47.2 (DOUT), D58.4 (DIN)
unnamed: D48.2 (DOUT), D59.4 (DIN)
unnamed: D49.2 (DOUT), D60.4 (DIN)
unnamed: D51.2 (DOUT), D61.4 (DIN)
unnamed: D52.2 (A), SW23.2
unnamed: D53.2 (A), SW24.2
unnamed: D54.2 (A), SW25.2
unnamed: D55.2 (A), SW26.2
unnamed: D56.2 (A), SW27.2
unnamed: D57.2 (DOUT), D67.4 (DIN)
unnamed: D9.4 (DIN), D58.2 (DOUT)
unnamed: D61.2 (DOUT), D68.4 (DIN)
unnamed: D62.2 (A), SW28.2
unnamed: D63.2 (A), SW29.2
unnamed: D64.2 (A), SW30.2
unnamed: D65.2 (A), SW31.2
unnamed: D66.2 (A), SW32.2
unnamed: D8.4 (DIN), D67.2 (DOUT)
unnamed: J1.1, SW2.2 (B)
unnamed: R1.2, U1.25 (P1.01-LF)
unnamed: R2.2, U1.27 (P1.07-LF)

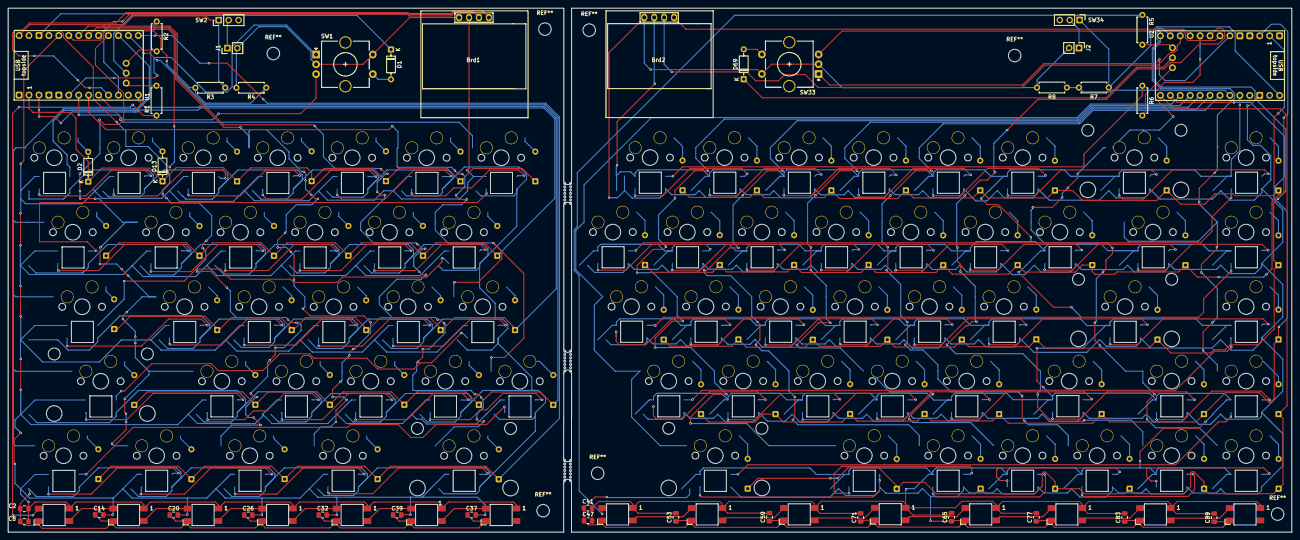
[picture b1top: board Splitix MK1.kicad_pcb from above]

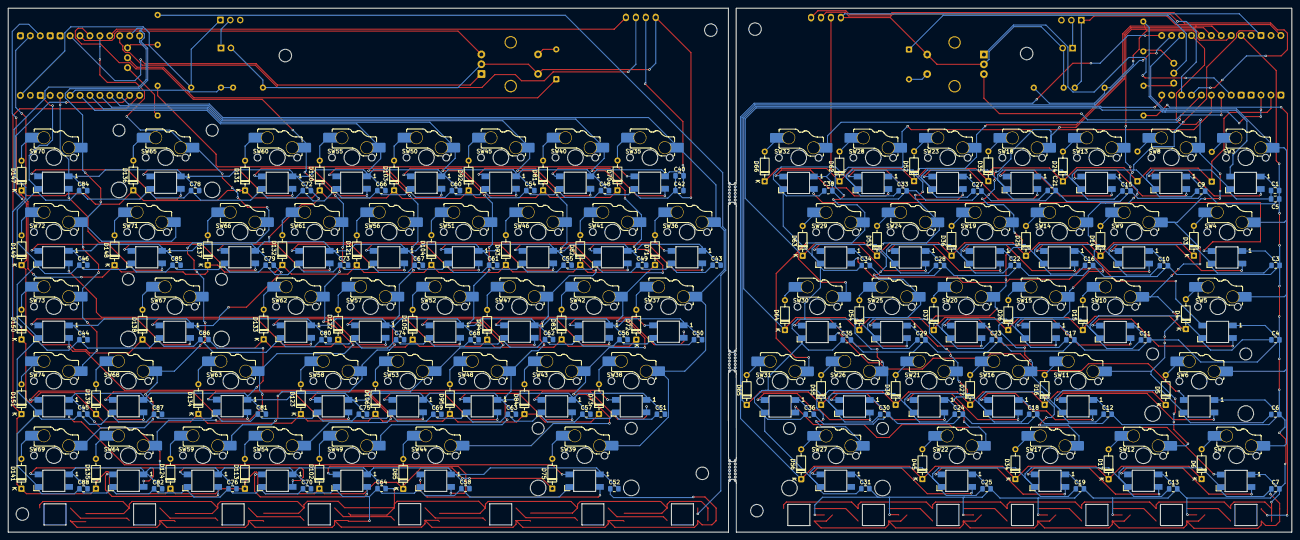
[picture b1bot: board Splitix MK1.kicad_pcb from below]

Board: 2 copper layers, 328.2 x 134.0 mm, 337 parts (280 on the bottom side), 206 nets.

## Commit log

2026-01-17 cad and 3d files
2026-01-27 adding pcb files
2026-01-27 added cad files
2026-03-21 Added BOM from KiCAD
2026-03-22 Adding final BOM for Splitix Mark - I
2026-03-23 Added README and assets
2026-03-23 Error fixing in README.md
2026-03-24 update files
2026-03-24 added left right step files
2026-03-24 added printing files
2026-03-24 added schematic pdf
2026-03-24 updated files
2026-03-24 updated BOM
2026-03-25 added layers
2026-03-25 added updated layer
2026-03-25 updated layer 0
2026-03-26 add splitix mk1 firmware
2026-03-26 added assembly files
2026-03-26 added files
2026-03-26 added step files
2026-03-26 added extra gerbers
2026-03-26 added production files
2026-03-26 file/folder cleanup
2026-03-26 file and folder restructure
2026-03-26 added step file format
